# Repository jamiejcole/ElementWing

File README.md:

## Element Wing - A DIY Command Wing for ETC EOS
This project is an extension of [my previous](https://github.com/jamiejcole/zenith) EOS controller that I made primarily for controlling moving head fixtures, as my Element 2 console doesn't have any encoder wheels.

It's a full sized EOS command wing, featuring the standard ETC key layout and 4 customisable rotary encoders.

### Components used
|             Part              | Qty | Total ($AUD) | Source |
|             ---               | --- | ------------ | ------ |
| Gateron Black Switches        | 90  | $31.19       | https://www.aliexpress.com/item/1005006376024657.html |
| Blank White XDA PBT Keycaps   | 90  | $34.00       | https://www.aliexpress.com/item/1005007683242914.html |
| 1N1418 THT Diodes             | 90  | $4.69        | https://www.aliexpress.com/item/32866531235.html      |
| MCP23017-E/SO                 | 1   | $12.59       | https://www.aliexpress.com/item/1005005066054098.html |
| Raspberry Pi Pico*            | 1   | $5.63        | https://www.aliexpress.com/item/1005006071676557.html |
| EC11 Rotary Encoders          | 4   | $5.20        | https://www.aliexpress.com/item/10000056483250.html   |
| Aluminium Knob for Encoders   | 4   | $11.39       | https://www.aliexpress.com/item/1005005207623966.html |
| Plastic Heat Set Inserts      | 6   | $14.99       | https://www.aliexpress.com/item/1005006472962973.html |
| **Total (excluding PCB)**     |     | **$119.68**  |                                                       |

> Note: The PCB design has the footprint for an official Raspberry Pi Pico with a micro-usb port. I wanted to have USB-C on my board, so I ordered the 16M variant of the above RP2040 board, without checking the pin layout. The board I ordered actually had a slightly different pin layout to the official Pi Pico so I had to make some jumps with short wire on the board, so if you use my PCB design, check which Pico you're ordering first!

## PCB Design
This was the first PCB I've designed, so apologies in advanced if I've made any silly mistakes on it. [Joe Scotto's video](https://www.youtube.com/watch?v=8WXpGTIbxlQ) was helpful for getting started with the design, and [iNimbleSloth's tutorials](https://www.youtube.com/watch?v=XKWoeBwpVNg) were also extremely useful for designing the keyswitch matrix. I ended up ordering the PCB from [JLCPCB](https://jlcpcb.com/) for around $100AUD including shipping, bringing the **total project cost to ~$220 AUD**.

The PCB consists of a 13x8 diode keyswitch matrix, where each row and column are connected to a GPIO pin on the Pico. The A/B/SW pins of each encoder are connected to a GPIO port on the MCP23017, which is connected to the Pico on the I2C0 interface, with the SDA and SCL lines pulled up to 3v3 with 2.2k resistors.

### Assembly process
After receiving the PCBs, I started designing some test layouts for the Cherry MX style switches. Due to the bed size of my 3D printer, I had to split up each piece into two parts, to be plastic welded together after printing. The CAD design consists of three main parts (each with left/right sides):
1. A plate for the switches to be inserted into prior to soldering to the PCB
2. A main case where the brass heat-set inserts will be put in, allowing the whole unit to be bolted together.
3. A top face-plate/cover with cut-outs for the switches and encoders.

### Custom Keycaps
The keycaps were made using a process I [found here](https://www.youtube.com/watch?v=JR1BwcFyexQ). I used blank white XDA profile PBT keycaps from aliexpress. The process was pretty straightforward:
- Cover each keycap in a thin layer of powder from a toner cartridge. I breathed on the keys before dunking them in the powder (the "hah hah" kind of breathing you do to clean glasses) to get the powder to stick better, then gently blew off the excess.
- Place keycap into a jig mounted to the laser engraver (this was done to ensure the text is consistently in the correct spot).
- Using a 15W diode laser at 380mm/min, 2.1% power and text on a fill layer at 300 lines/inch, etched the dye into the keycaps.
- Cleaned off the excess powder with warm water.

### Programming the microcontroller
I decided to use a Raspberry Pi Pico rather than an Arduino or ESP8266 due to the amount of GPIO pins it had. I downloaded [Earle Philhower's Arduino Core](https://github.com/earlephilhower/arduino-pico) for RP2040 boards and uploaded a test sketch using the Arduino IDE. The Pico uses OSC to communicate with EOS over the USB Serial interface. More info about OSC [can be found here](https://github.com/cnmat/osc). 

The [ETC #lighthack](https://github.com/ETCLabs/lighthack) community also was extremely helpful. Big thanks to [sstaub](https://github.com/CNMAT/OSC/issues/159#issuecomment-2566483844) over on the OSC repo.

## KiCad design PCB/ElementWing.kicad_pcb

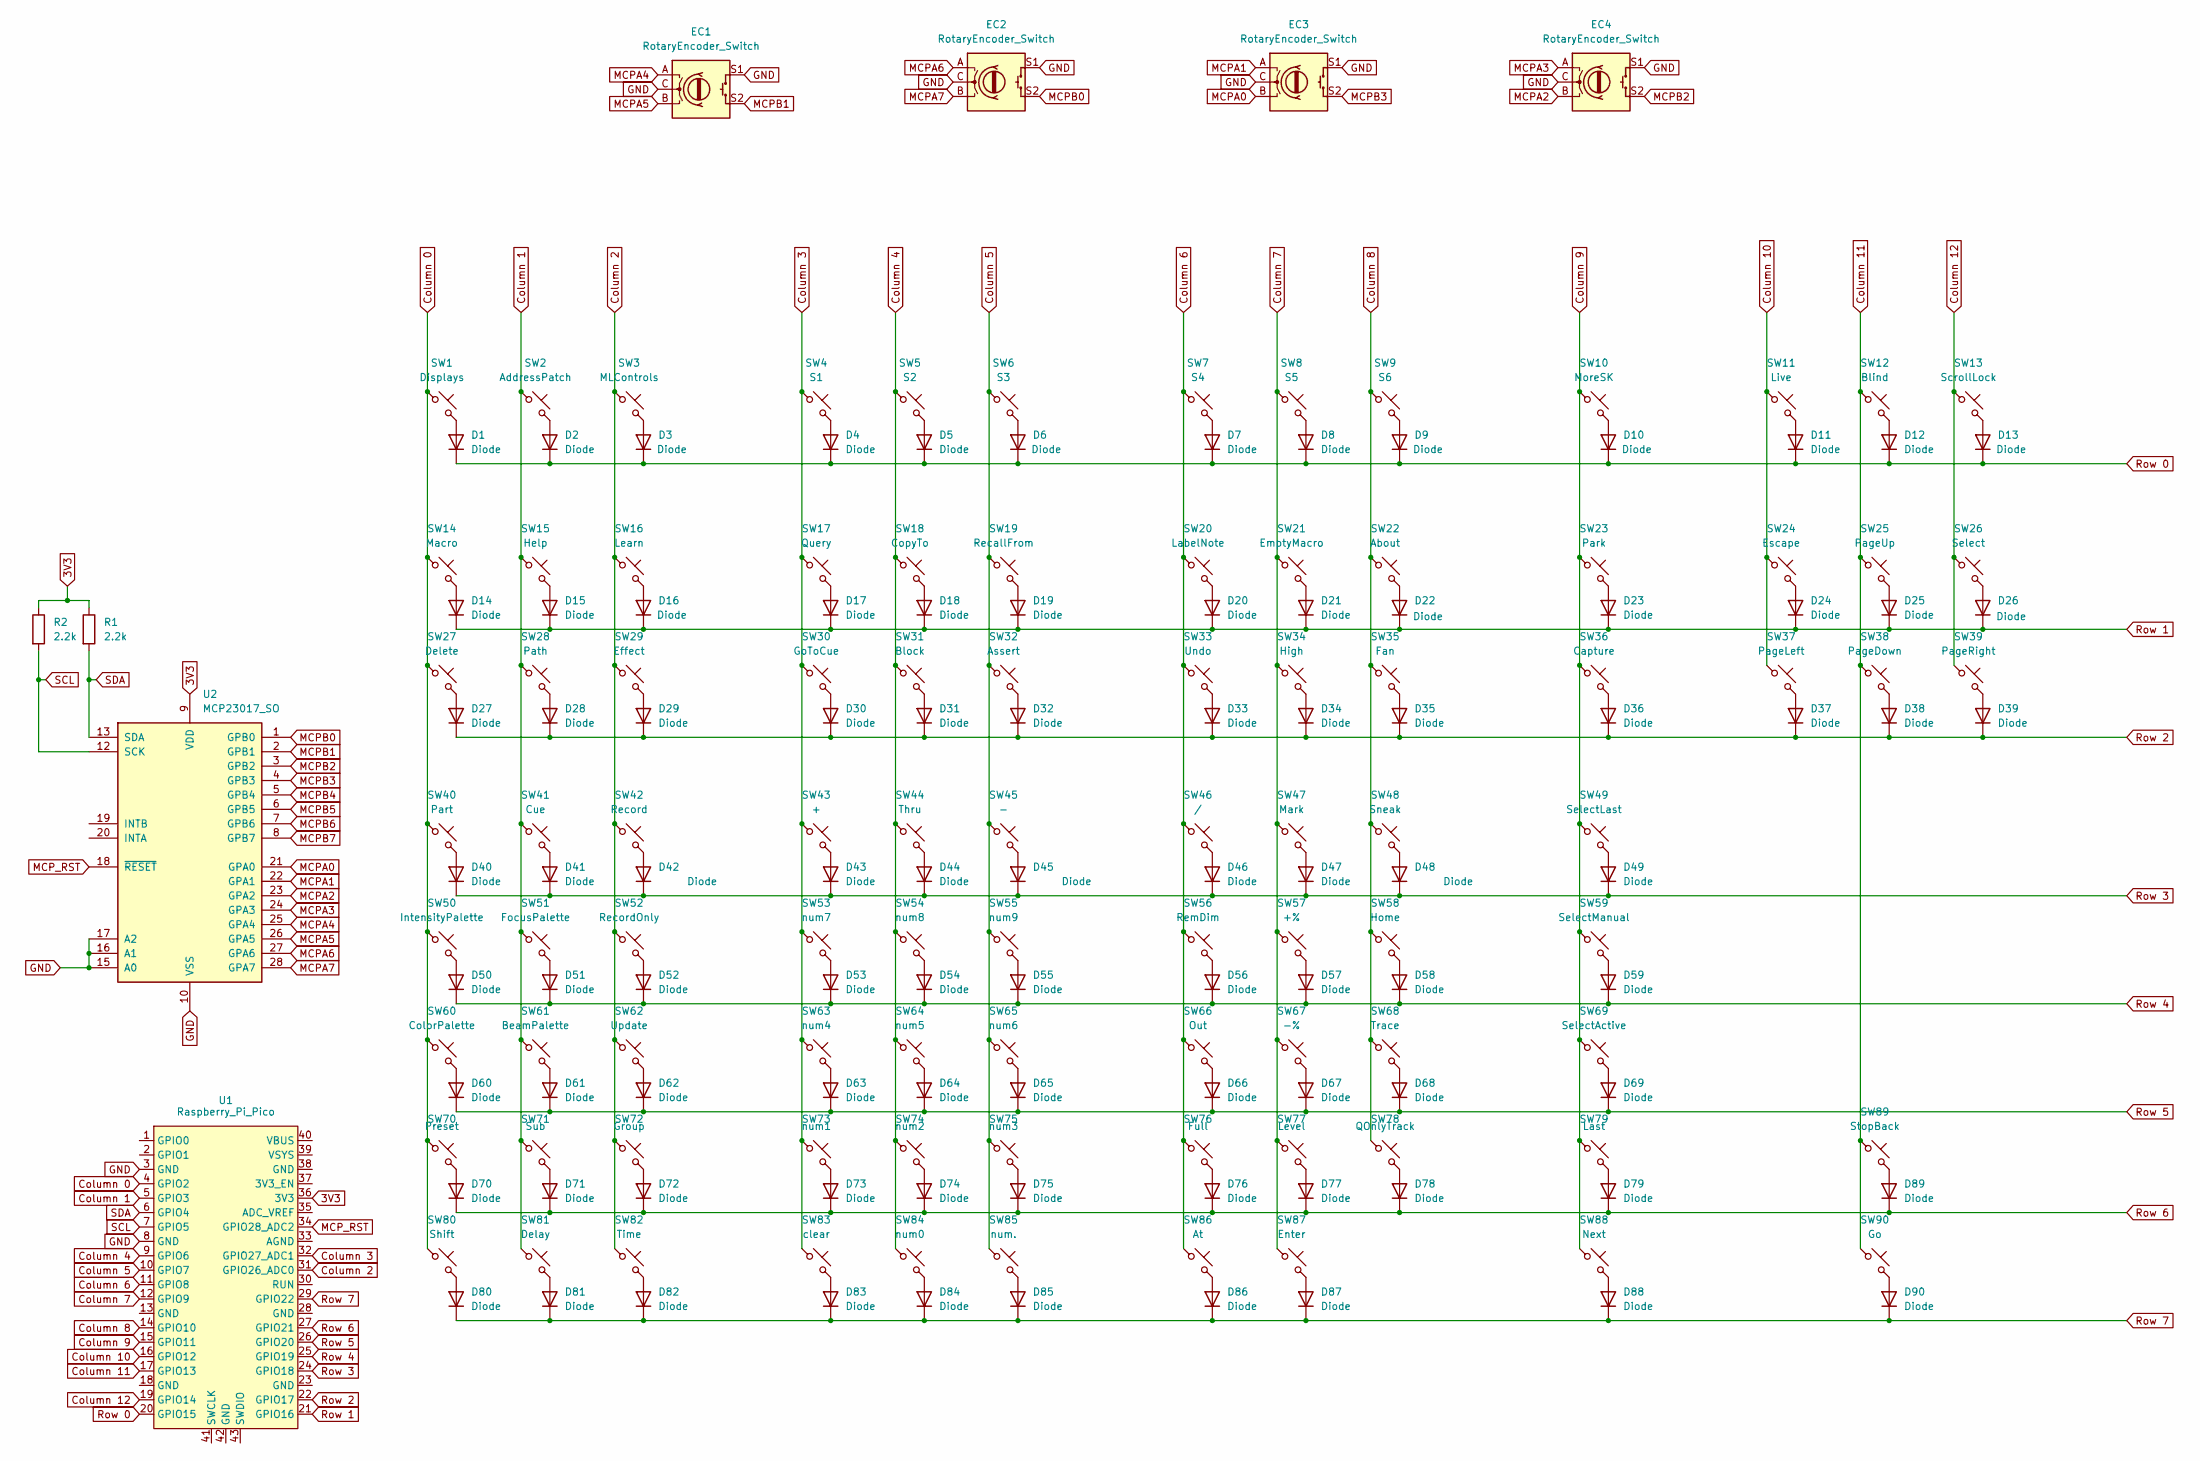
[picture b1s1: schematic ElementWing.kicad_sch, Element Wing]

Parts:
D1, D2, D3, D4, D5, D6, D7, D8, D9, D10, D11, D12, D13, D14, D15, D16, D17, D18, D19, D20, D21, D22, D23, D24, D25, D26, D27, D28, D29, D30, D31, D32, D33, D34, D35, D36, D37, D38, D39, D40, D41, D42, D43, D44, D45, D46, D47, D48, D49, D50, D51, D52, D53, D54, D55, D56, D57, D58, D59, D60, D61, D62, D63, D64, D65, D66, D67, D68, D69, D70, D71, D72, D73, D74, D75, D76, D77, D78, D79, D80, D81, D82, D83, D84, D85, D86, D87, D88, D89, D90: Diode; Diode_DO-35
EC1, EC2, EC3, EC4: RotaryEncoder_Switch; RotaryEncoder_Alps_EC11E-Switch_Vertical_H20mm
R1, R2: 2.2k; R_Axial_DIN0207_L6.3mm_D2.5mm_P10.16mm_Horizontal
SW1: Displays; MX_PCB_1.00u
SW2: AddressPatch; MX_PCB_1.00u
SW3: MLControls; MX_PCB_1.00u
SW4: S1; MX_PCB_1.00u
SW5: S2; MX_PCB_1.00u
SW6: S3; MX_PCB_1.00u
SW7: S4; MX_PCB_1.00u
SW8: S5; MX_PCB_1.00u
SW9: S6; MX_PCB_1.00u
SW10: MoreSK; MX_PCB_1.00u
SW11: Live; MX_PCB_1.00u
SW12: Blind; MX_PCB_1.00u
SW13: ScrollLock; MX_PCB_1.00u
SW14: Macro; MX_PCB_1.00u
SW15: Help; MX_PCB_1.00u
SW16: Learn; MX_PCB_1.00u
SW17: Query; MX_PCB_1.00u
SW18: CopyTo; MX_PCB_1.00u
SW19: RecallFrom; MX_PCB_1.00u
SW20: LabelNote; MX_PCB_1.00u
SW21: EmptyMacro; MX_PCB_1.00u
SW22: About; MX_PCB_1.00u
SW23: Park; MX_PCB_1.00u
SW24: Escape; MX_PCB_1.00u
SW25: PageUp; MX_PCB_1.00u
SW26: Select; MX_PCB_1.00u
SW27: Delete; MX_PCB_1.00u
SW28: Path; MX_PCB_1.00u
SW29: Effect; MX_PCB_1.00u
SW30: GoToCue; MX_PCB_1.00u
SW31: Block; MX_PCB_1.00u
SW32: Assert; MX_PCB_1.00u
SW33: Undo; MX_PCB_1.00u
SW34: High; MX_PCB_1.00u
SW35: Fan; MX_PCB_1.00u
SW36: Capture; MX_PCB_1.00u
SW37: PageLeft; MX_PCB_1.00u
SW38: PageDown; MX_PCB_1.00u
SW39: PageRight; MX_PCB_1.00u
SW40: Part; MX_PCB_1.00u
SW41: Cue; MX_PCB_1.00u
SW42: Record; MX_PCB_1.00u
SW43: +; MX_PCB_1.00u
SW44: Thru; MX_PCB_1.00u
SW45: -; MX_PCB_1.00u
SW46: /; MX_PCB_1.00u
SW47: Mark; MX_PCB_1.00u
SW48: Sneak; MX_PCB_1.00u
SW49: SelectLast; MX_PCB_1.00u
SW50: IntensityPalette; MX_PCB_1.00u
SW51: FocusPalette; MX_PCB_1.00u
SW52: RecordOnly; MX_PCB_1.00u
SW53: num7; MX_PCB_1.00u
SW54: num8; MX_PCB_1.00u
SW55: num9; MX_PCB_1.00u
SW56: RemDim; MX_PCB_1.00u
SW57: +%; MX_PCB_1.00u
SW58: Home; MX_PCB_1.00u
SW59: SelectManual; MX_PCB_1.00u
SW60: ColorPalette; MX_PCB_1.00u
SW61: BeamPalette; MX_PCB_1.00u
SW62: Update; MX_PCB_1.00u
SW63: num4; MX_PCB_1.00u
SW64: num5; MX_PCB_1.00u
SW65: num6; MX_PCB_1.00u
SW66: Out; MX_PCB_1.00u
SW67: -%; MX_PCB_1.00u
SW68: Trace; MX_PCB_1.00u
SW69: SelectActive; MX_PCB_1.00u
SW70: Preset; MX_PCB_1.00u
SW71: Sub; MX_PCB_1.00u
SW72: Group; MX_PCB_1.00u
SW73: num1; MX_PCB_1.00u
SW74: num2; MX_PCB_1.00u
SW75: num3; MX_PCB_1.00u
SW76: Full; MX_PCB_1.00u
SW77: Level; MX_PCB_1.00u
SW78: QOnlyTrack; MX_PCB_1.00u
SW79: Last; MX_PCB_1.00u
SW80: Shift; MX_PCB_1.00u
SW81: Delay; MX_PCB_1.00u
SW82: Time; MX_PCB_1.00u
SW83: clear; MX_PCB_1.00u
SW84: num0; MX_PCB_1.00u
SW85: num.; MX_PCB_1.00u
SW86: At; MX_PCB_1.00u
SW87: Enter; MX_PCB_1.00u
SW88: Next; MX_PCB_1.00u
SW89: StopBack; MX_PCB_1.00u
SW90: Go; MX_PCB_1.00u
U1: Raspberry_Pi_Pico
U2: MCP23017_SO; SOIC-28W_7.5x17.9mm_P1.27mm

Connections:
3V3: R1.1, R2.1, U1.36 (3V3), U2.9 (VDD)
Column 0: SW1.1, SW14.1, SW27.1, SW40.1, SW50.1, SW60.1, SW70.1, SW80.1, U1.4 (GPIO2)
Column 1: SW2.1, SW15.1, SW28.1, SW41.1, SW51.1, SW61.1, SW71.1, SW81.1, U1.5 (GPIO3)
Column 2: SW3.1, SW16.1, SW29.1, SW42.1, SW52.1, SW62.1, SW72.1, SW82.1, U1.31 (GPIO26_ADC0)
Column 3: SW4.1, SW17.1, SW30.1, SW43.1, SW53.1, SW63.1, SW73.1, SW83.1, U1.32 (GPIO27_ADC1)
Column 4: SW5.1, SW18.1, SW31.1, SW44.1, SW54.1, SW64.1, SW74.1, SW84.1, U1.9 (GPIO6)
Column 5: SW6.1, SW19.1, SW32.1, SW45.1, SW55.1, SW65.1, SW75.1, SW85.1, U1.10 (GPIO7)
Column 6: SW7.1, SW20.1, SW33.1, SW46.1, SW56.1, SW66.1, SW76.1, SW86.1, U1.11 (GPIO8)
Column 7: SW8.1, SW21.1, SW34.1, SW47.1, SW57.1, SW67.1, SW77.1, SW87.1, U1.12 (GPIO9)
Column 8: SW9.1, SW22.1, SW35.1, SW48.1, SW58.1, SW68.1, SW78.1, U1.14 (GPIO10)
Column 9: SW10.1, SW23.1, SW36.1, SW49.1, SW59.1, SW69.1, SW79.1, SW88.1, U1.15 (GPIO11)
Column 10: SW11.1, SW24.1, SW37.1, U1.16 (GPIO12)
Column 11: SW12.1, SW25.1, SW38.1, SW89.1, SW90.1, U1.17 (GPIO13)
Column 12: SW13.1, SW26.1, SW39.1, U1.19 (GPIO14)
GND: EC1.C, EC1.S1, EC2.C, EC2.S1, EC3.C, EC3.S1, EC4.C, EC4.S1, U1.3 (GND), U1.8 (GND), U2.10 (VSS), U2.15 (A0), U2.16 (A1), U2.17 (A2)
MCPA0: EC3.B, U2.21 (GPA0)
MCPA1: EC3.A, U2.22 (GPA1)
MCPA2: EC4.B, U2.23 (GPA2)
MCPA3: EC4.A, U2.24 (GPA3)
MCPA4: EC1.A, U2.25 (GPA4)
MCPA5: EC1.B, U2.26 (GPA5)
MCPA6: EC2.A, U2.27 (GPA6)
MCPA7: EC2.B, U2.28 (GPA7)
MCPB0: EC2.S2, U2.1 (GPB0)
MCPB1: EC1.S2, U2.2 (GPB1)
MCPB2: EC4.S2, U2.3 (GPB2)
MCPB3: EC3.S2, U2.4 (GPB3)
MCPB4: U2.5 (GPB4)
MCPB5: U2.6 (GPB5)
MCPB6: U2.7 (GPB6)
MCPB7: U2.8 (GPB7)
MCP_RST: U1.34 (GPIO28_ADC2), U2.18 (~RESET)
unnamed: D1.2 (A), SW1.2
unnamed: D2.2 (A), SW2.2
unnamed: D3.2 (A), SW3.2
unnamed: D4.2 (A), SW4.2
unnamed: D5.2 (A), SW5.2
unnamed: D6.2 (A), SW6.2
unnamed: D7.2 (A), SW7.2
unnamed: D8.2 (A), SW8.2
unnamed: D9.2 (A), SW9.2
unnamed: D10.2 (A), SW10.2
unnamed: D11.2 (A), SW11.2
unnamed: D12.2 (A), SW12.2
unnamed: D13.2 (A), SW13.2
unnamed: D14.2 (A), SW14.2
unnamed: D15.2 (A), SW15.2
unnamed: D16.2 (A), SW16.2
unnamed: D17.2 (A), SW17.2
unnamed: D18.2 (A), SW18.2
unnamed: D19.2 (A), SW19.2
unnamed: D20.2 (A), SW20.2
unnamed: D21.2 (A), SW21.2
unnamed: D22.2 (A), SW22.2
unnamed: D23.2 (A), SW23.2
unnamed: D24.2 (A), SW24.2
unnamed: D25.2 (A), SW25.2
unnamed: D26.2 (A), SW26.2
unnamed: D27.2 (A), SW27.2
unnamed: D28.2 (A), SW28.2
unnamed: D29.2 (A), SW29.2
unnamed: D30.2 (A), SW30.2
unnamed: D31.2 (A), SW31.2
unnamed: D32.2 (A), SW32.2
unnamed: D33.2 (A), SW33.2
unnamed: D34.2 (A), SW34.2
unnamed: D35.2 (A), SW35.2
unnamed: D36.2 (A), SW36.2
unnamed: D37.2 (A), SW37.2
unnamed: D38.2 (A), SW38.2
unnamed: D39.2 (A), SW39.2
unnamed: D40.2 (A), SW40.2
unnamed: D41.2 (A), SW41.2
unnamed: D42.2 (A), SW42.2
unnamed: D43.2 (A), SW43.2
unnamed: D44.2 (A), SW44.2
unnamed: D45.2 (A), SW45.2
unnamed: D46.2 (A), SW46.2
unnamed: D47.2 (A), SW47.2
unnamed: D48.2 (A), SW48.2
unnamed: D49.2 (A), SW49.2
unnamed: D50.2 (A), SW50.2
unnamed: D51.2 (A), SW51.2
unnamed: D52.2 (A), SW52.2
unnamed: D53.2 (A), SW53.2
unnamed: D54.2 (A), SW54.2
unnamed: D55.2 (A), SW55.2
unnamed: D56.2 (A), SW56.2
unnamed: D57.2 (A), SW57.2
unnamed: D58.2 (A), SW58.2
unnamed: D59.2 (A), SW59.2
unnamed: D60.2 (A), SW60.2
unnamed: D61.2 (A), SW61.2
unnamed: D62.2 (A), SW62.2
unnamed: D63.2 (A), SW63.2
unnamed: D64.2 (A), SW64.2
unnamed: D65.2 (A), SW65.2
unnamed: D66.2 (A), SW66.2
unnamed: D67.2 (A), SW67.2
unnamed: D68.2 (A), SW68.2
unnamed: D69.2 (A), SW69.2
unnamed: D70.2 (A), SW70.2
unnamed: D71.2 (A), SW71.2
unnamed: D72.2 (A), SW72.2
unnamed: D73.2 (A), SW73.2
unnamed: D74.2 (A), SW74.2
unnamed: D75.2 (A), SW75.2
unnamed: D76.2 (A), SW76.2
unnamed: D77.2 (A), SW77.2
unnamed: D78.2 (A), SW78.2
unnamed: D79.2 (A), SW79.2
unnamed: D80.2 (A), SW80.2
unnamed: D81.2 (A), SW81.2
unnamed: D82.2 (A), SW82.2
unnamed: D83.2 (A), SW83.2
unnamed: D84.2 (A), SW84.2
unnamed: D85.2 (A), SW85.2
unnamed: D86.2 (A), SW86.2
unnamed: D87.2 (A), SW87.2
unnamed: D88.2 (A), SW88.2
unnamed: D89.2 (A), SW89.2
unnamed: D90.2 (A), SW90.2
Row 0: D1.1 (K), D2.1 (K), D3.1 (K), D4.1 (K), D5.1 (K), D6.1 (K), D7.1 (K), D8.1 (K), D9.1 (K), D10.1 (K), D11.1 (K), D12.1 (K), D13.1 (K), U1.20 (GPIO15)
Row 1: D14.1 (K), D15.1 (K), D16.1 (K), D17.1 (K), D18.1 (K), D19.1 (K), D20.1 (K), D21.1 (K), D22.1 (K), D23.1 (K), D24.1 (K), D25.1 (K), D26.1 (K), U1.21 (GPIO16)
Row 2: D27.1 (K), D28.1 (K), D29.1 (K), D30.1 (K), D31.1 (K), D32.1 (K), D33.1 (K), D34.1 (K), D35.1 (K), D36.1 (K), D37.1 (K), D38.1 (K), D39.1 (K), U1.22 (GPIO17)
Row 3: D40.1 (K), D41.1 (K), D42.1 (K), D43.1 (K), D44.1 (K), D45.1 (K), D46.1 (K), D47.1 (K), D48.1 (K), D49.1 (K), U1.24 (GPIO18)
Row 4: D50.1 (K), D51.1 (K), D52.1 (K), D53.1 (K), D54.1 (K), D55.1 (K), D56.1 (K), D57.1 (K), D58.1 (K), D59.1 (K), U1.25 (GPIO19)
Row 5: D60.1 (K), D61.1 (K), D62.1 (K), D63.1 (K), D64.1 (K), D65.1 (K), D66.1 (K), D67.1 (K), D68.1 (K), D69.1 (K), U1.26 (GPIO20)
Row 6: D70.1 (K), D71.1 (K), D72.1 (K), D73.1 (K), D74.1 (K), D75.1 (K), D76.1 (K), D77.1 (K), D78.1 (K), D79.1 (K), D89.1 (K), U1.27 (GPIO21)
Row 7: D80.1 (K), D81.1 (K), D82.1 (K), D83.1 (K), D84.1 (K), D85.1 (K), D86.1 (K), D87.1 (K), D88.1 (K), D90.1 (K), U1.29 (GPIO22)
SCL: R2.2, U1.7 (GPIO5), U2.12 (SCK)
SDA: R1.2, U1.6 (GPIO4), U2.13 (SDA)

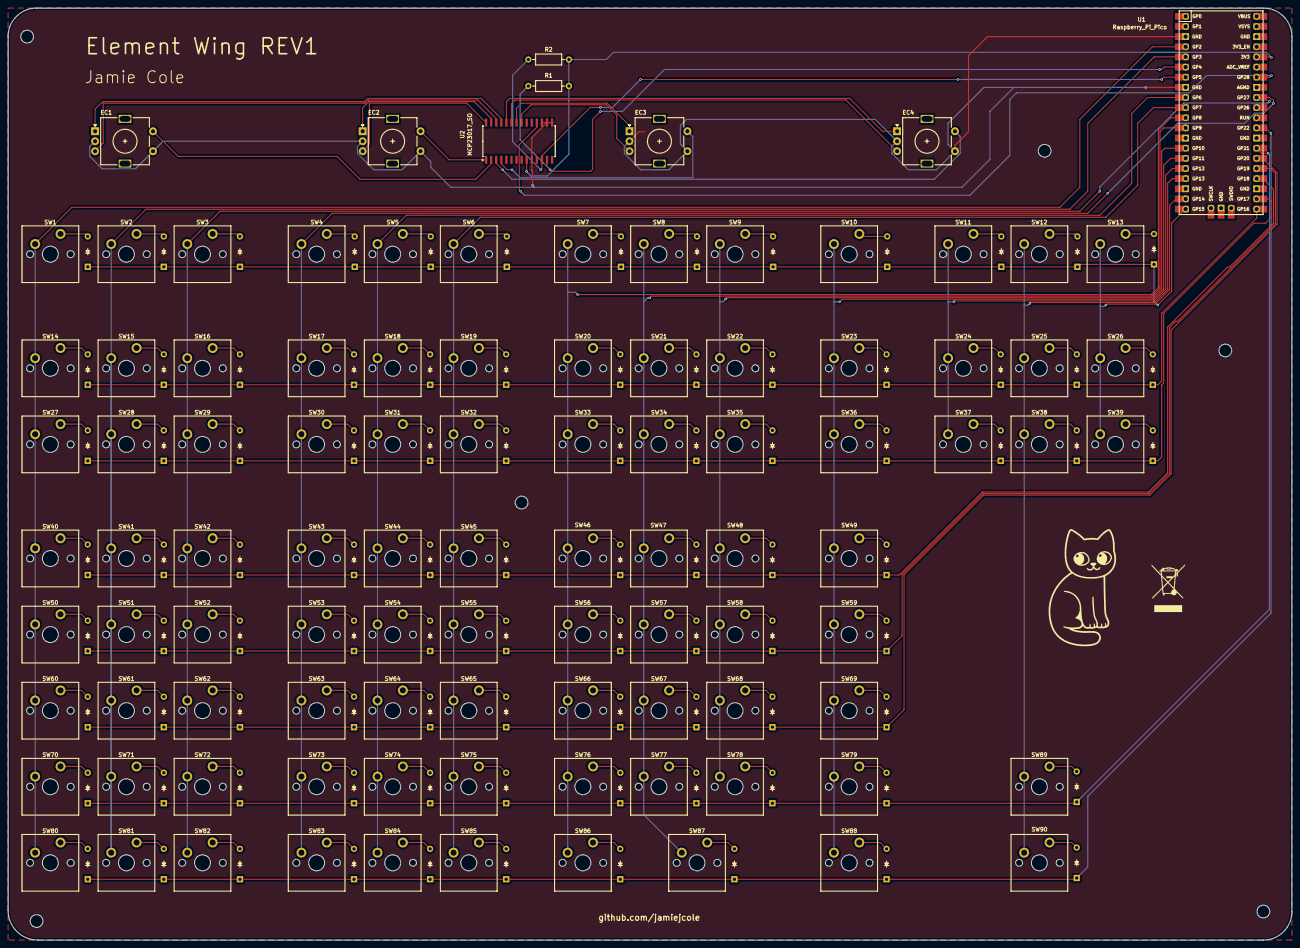
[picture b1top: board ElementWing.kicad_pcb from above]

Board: 2 copper layers, 321.5 x 233.4 mm, 188 parts (0 on the bottom side), 128 nets.

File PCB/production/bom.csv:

Designator,Footprint,Quantity,Value,LCSC Part #
"D1, D10, D11, D12, D13, D14, D15, D16, D17, D18, D19, D2, D20, D21, D22, D23, D24, D25, D26, D27, D28, D29, D3, D30, D31, D32, D33, D34, D35, D36, D37, D38, D39, D4, D40, D41, D42, D43, D44, D45, D46, D47, D48, D49, D5, D50, D51, D52, D53, D54, D55, D56, D57, D58, D59, D6, D60, D61, D62, D63, D64, D65, D66, D67, D68, D69, D7, D70, D71, D72, D73, D74, D75, D76, D77, D78, D79, D8, D80, D81, D82, D83, D84, D85, D86, D87, D88, D89, D9, D90",Diode_DO-35,90,Diode,
"EC1, EC2, EC3, EC4",RotaryEncoder_Alps_EC11E-Switch_Vertical_H20mm,4,RotaryEncoder_Switch,
"R1, R2",R_Axial_DIN0207_L6.3mm_D2.5mm_P10.16mm_Horizontal,2,2.2k,
SW1,MX_PCB_1.00u,1,Displays,
SW10,MX_PCB_1.00u,1,MoreSK,
SW11,MX_PCB_1.00u,1,Live,
SW12,MX_PCB_1.00u,1,Blind,
SW13,MX_PCB_1.00u,1,ScrollLock,
SW14,MX_PCB_1.00u,1,Macro,
SW15,MX_PCB_1.00u,1,Help,
SW16,MX_PCB_1.00u,1,Learn,
SW17,MX_PCB_1.00u,1,Query,
SW18,MX_PCB_1.00u,1,CopyTo,
SW19,MX_PCB_1.00u,1,RecallFrom,
SW2,MX_PCB_1.00u,1,AddressPatch,
SW20,MX_PCB_1.00u,1,LabelNote,
SW21,MX_PCB_1.00u,1,EmptyMacro,
SW22,MX_PCB_1.00u,1,About,
SW23,MX_PCB_1.00u,1,Park,
SW24,MX_PCB_1.00u,1,Escape,
SW25,MX_PCB_1.00u,1,PageUp,
SW26,MX_PCB_1.00u,1,Select,
SW27,MX_PCB_1.00u,1,Delete,
SW28,MX_PCB_1.00u,1,Path,
SW29,MX_PCB_1.00u,1,Effect,
SW3,MX_PCB_1.00u,1,MLControls,
SW30,MX_PCB_1.00u,1,GoToCue,
SW31,MX_PCB_1.00u,1,Block,
SW32,MX_PCB_1.00u,1,Assert,
SW33,MX_PCB_1.00u,1,Undo,
SW34,MX_PCB_1.00u,1,High,
SW35,MX_PCB_1.00u,1,Fan,
SW36,MX_PCB_1.00u,1,Capture,
SW37,MX_PCB_1.00u,1,PageLeft,
SW38,MX_PCB_1.00u,1,PageDown,
SW39,MX_PCB_1.00u,1,PageRight,
SW4,MX_PCB_1.00u,1,S1,
SW40,MX_PCB_1.00u,1,Part,
SW41,MX_PCB_1.00u,1,Cue,
SW42,MX_PCB_1.00u,1,Record,
SW43,MX_PCB_1.00u,1,+,
SW44,MX_PCB_1.00u,1,Thru,
SW45,MX_PCB_1.00u,1,-,
SW46,MX_PCB_1.00u,1,/,
SW47,MX_PCB_1.00u,1,Mark,
SW48,MX_PCB_1.00u,1,Sneak,
SW49,MX_PCB_1.00u,1,SelectLast,
SW5,MX_PCB_1.00u,1,S2,
SW50,MX_PCB_1.00u,1,IntensityPalette,
SW51,MX_PCB_1.00u,1,FocusPalette,
SW52,MX_PCB_1.00u,1,RecordOnly,
SW53,MX_PCB_1.00u,1,num7,
SW54,MX_PCB_1.00u,1,num8,
SW55,MX_PCB_1.00u,1,num9,
SW56,MX_PCB_1.00u,1,RemDim,
SW57,MX_PCB_1.00u,1,+%,
SW58,MX_PCB_1.00u,1,Home,
SW59,MX_PCB_1.00u,1,SelectManual,
SW6,MX_PCB_1.00u,1,S3,
SW60,MX_PCB_1.00u,1,ColorPalette,
SW61,MX_PCB_1.00u,1,BeamPalette,
SW62,MX_PCB_1.00u,1,Update,
SW63,MX_PCB_1.00u,1,num4,
SW64,MX_PCB_1.00u,1,num5,
SW65,MX_PCB_1.00u,1,num6,
SW66,MX_PCB_1.00u,1,Out,
SW67,MX_PCB_1.00u,1,-%,
SW68,MX_PCB_1.00u,1,Trace,
SW69,MX_PCB_1.00u,1,SelectActive,
SW7,MX_PCB_1.00u,1,S4,
SW70,MX_PCB_1.00u,1,Preset,
SW71,MX_PCB_1.00u,1,Sub,
SW72,MX_PCB_1.00u,1,Group,
SW73,MX_PCB_1.00u,1,num1,
SW74,MX_PCB_1.00u,1,num2,
SW75,MX_PCB_1.00u,1,num3,
SW76,MX_PCB_1.00u,1,Full,
SW77,MX_PCB_1.00u,1,Level,
SW78,MX_PCB_1.00u,1,QOnlyTrack,
SW79,MX_PCB_1.00u,1,Last,
SW8,MX_PCB_1.00u,1,S5,
SW80,MX_PCB_1.00u,1,Shift,
SW81,MX_PCB_1.00u,1,Delay,
SW82,MX_PCB_1.00u,1,Time,
SW83,MX_PCB_1.00u,1,clear,
SW84,MX_PCB_1.00u,1,num0,
SW85,MX_PCB_1.00u,1,num.,
SW86,MX_PCB_1.00u,1,At,
SW87,MX_PCB_1.00u,1,Enter,
SW88,MX_PCB_1.00u,1,Next,
SW89,MX_PCB_1.00u,1,StopBack,
SW9,MX_PCB_1.00u,1,S6,
SW90,MX_PCB_1.00u,1,Go,
U1,Raspberry_Pi_Pico,1,Raspberry_Pi_Pico,
U2,SOIC-28W_7.5x17.9mm_P1.27mm,1,MCP23017_SO,

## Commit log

2025-01-03 added code
2025-01-04 fixed OSC commands and updated readme
2025-01-04 updated gitignore
2025-01-04 Updated page functions
2025-01-04 added CAD and PCB designs
2025-01-04 Added STLs
2025-12-14 fixed blind on startup
2026-02-17 Keycap layout
